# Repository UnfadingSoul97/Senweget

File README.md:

# ⌨️Senweget⌨️
## A split Corne Keyboard that doubles as a stenograph and a fun fidget which your can customise yourself.
Here ig it will look good cute frog keycaps.

Link to Project:https://cad.onshape.com/documents/2615d6a32fd601db65ed9c82/w/49b2a2fd03e5ba3a97975127/e/aca29c1b2985c1fb6079fbe5

---
I was just living my life and i thought hey i can make stuff in cad now and wanted to push my limit and wanted to make something that was not too hard but still new to make.
The tracing process was probably the hardest part i had to experience in this project.

### What does it do??

 It can be used for stenograph,Hotswappable but it HAS **PER-KEY RGB** not that it matters but need to see at Night.
 And can Play Music 🎵
 You can add 🎹,🥁 and you can add custom sounds. One thing am using buzzer cuz i like its buzzing and it cool.
 For ya nerds who know what you are doing.I have left some free GPIOS for connecting stuff ya like.

 ### THE BIRTH 🐵
 I made the Schematic and PCB in KICAD
 **Schematic**

**PCB Design**

**PCB**

## 📋 Frimware
For now i only added for qwerty cuz i really hate writing readme cuz think ADHD idk not tested.
Any way it has standared Qwerty and 1 Knob on each side 
Left one does volume up and down with click as mute
Right one does handles and click also does mute cuz why not.

## How to set up 
Take the bezzle and put on top on the top of the pcb and add your low profile switches then place it on top of the main body according to the tabs then place in the pcb and bexzzle.
and screw it from under the case using 5 M3 screws.the MCU should be facing down on the right side(which means its usb c should face to the downwared direction from the underside of the pcb.
For the left side the top should be facing todwards the pcb and under the PCB ofc
1.Take the PCB and add your switches.
2.Put i it on the body.
 for the right side pcb put the mcu under the pcb which should be facing away form the pcb.
 for the left one the Mcu should be facing towards the pcb otherwise the usb c wont fit.
3.now place in the top bezzle
4.Now u can screw it from the underneath using M3. screw pls check the length of the screw needed cuz idk the exact height after printing.

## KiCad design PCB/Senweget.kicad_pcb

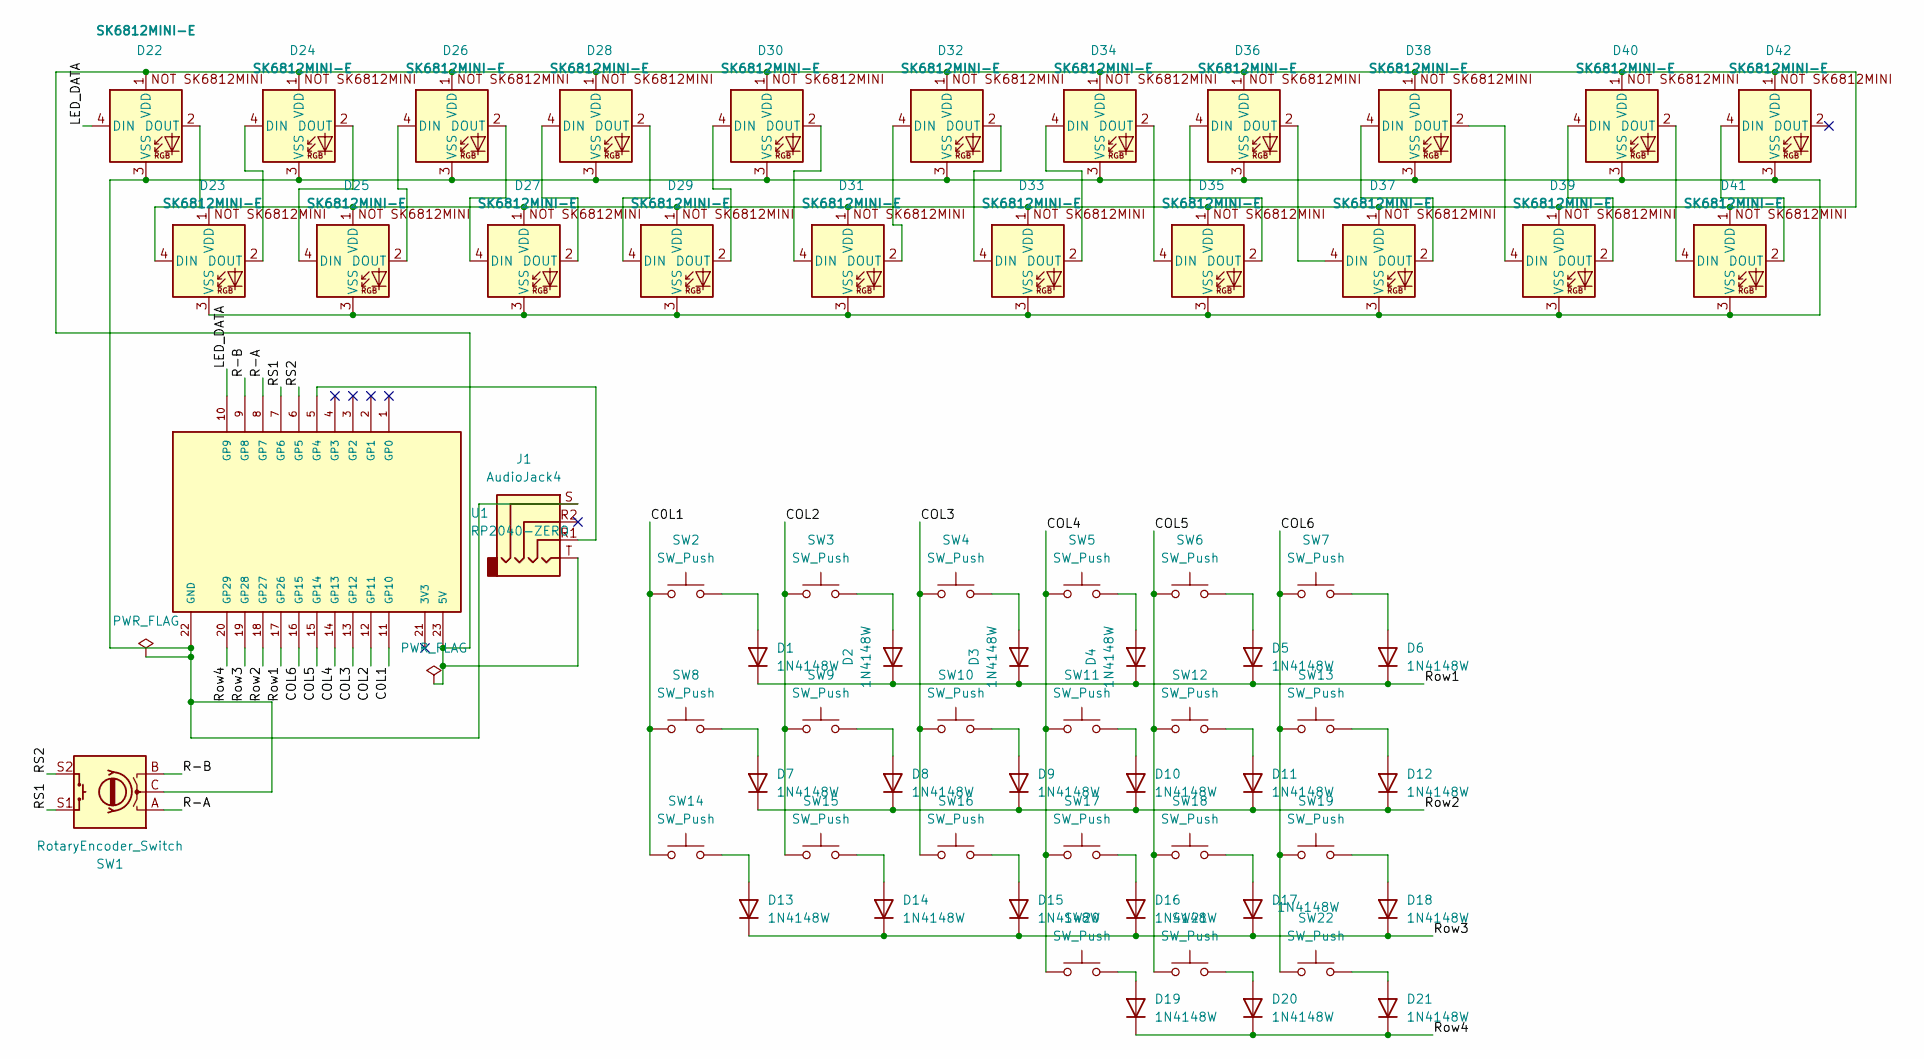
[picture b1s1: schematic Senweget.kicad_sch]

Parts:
D1, D2, D3, D4, D5, D6, D7, D8, D9, D10, D11, D12, D13, D14, D15, D16, D17, D18, D19, D20, D21: 1N4148W; D_SOD-123
D22, D23, D24, D25, D26, D27, D28, D29, D30, D31, D32, D33, D34, D35, D36, D37, D38, D39, D40, D41, D42: SK6812MINI-E; LED_SK6812MINI-E_3.2x2.8mm_P1.5mm_ReverseMount
J1: AudioJack4; Jack_3.5mm_PJ320D_Horizontal
SW1: RotaryEncoder_Switch; RotaryEncoder_Alps_EC11E-Switch_Vertical_H20mm
SW2, SW3, SW4, SW5, SW6, SW7, SW8, SW9, SW10, SW11, SW12, SW13, SW14, SW15, SW16, SW17, SW18, SW19, SW20, SW21, SW22: SW_Push; SW_MX_Kailh_Choc_V1V2_HotSwap_Hybrid_double
U1: RP2040-ZERO; MODULE_RP2040-ZERO; PARTREV NA

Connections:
/C0L1: SW2.1, SW8.1, SW14.1, U1.11 (GP10)
/COL2: SW3.1, SW9.1, SW15.1, U1.12 (GP11)
/COL3: SW4.1, SW10.1, SW16.1, U1.13 (GP12)
/COL4: SW5.1, SW11.1, SW17.1, SW20.1, U1.14 (GP13)
/COL5: SW6.1, SW12.1, SW18.1, SW21.1, U1.15 (GP14)
/COL6: SW7.1, SW13.1, SW19.1, SW22.1, U1.16 (GP15)
/LED_DATA: D22.4 (DIN), U1.10 (GP9)
/R-A: SW1.A, U1.8 (GP7)
/R-B: SW1.B, U1.9 (GP8)
/RS1: SW1.S1, U1.7 (GP6)
/RS2: SW1.S2, U1.6 (GP5)
/Row1: D1.1 (K), D2.1 (K), D3.1 (K), D4.1 (K), D5.1 (K), D6.1 (K), U1.17 (GP26)
/Row2: D7.1 (K), D8.1 (K), D9.1 (K), D10.1 (K), D11.1 (K), D12.1 (K), U1.18 (GP27)
/Row3: D13.1 (K), D14.1 (K), D15.1 (K), D16.1 (K), D17.1 (K), D18.1 (K), U1.19 (GP28)
/Row4: D19.1 (K), D20.1 (K), D21.1 (K), U1.20 (GP29)
unnamed: D1.2 (A), SW2.2
unnamed: D2.2 (A), SW3.2
unnamed: D3.2 (A), SW4.2
unnamed: D4.2 (A), SW5.2
unnamed: D5.2 (A), SW6.2
unnamed: D6.2 (A), SW7.2
unnamed: D7.2 (A), SW8.2
unnamed: D8.2 (A), SW9.2
unnamed: D9.2 (A), SW10.2
unnamed: D10.2 (A), SW11.2
unnamed: D11.2 (A), SW12.2
unnamed: D12.2 (A), SW13.2
unnamed: D13.2 (A), SW14.2
unnamed: D14.2 (A), SW15.2
unnamed: D15.2 (A), SW16.2
unnamed: D16.2 (A), SW17.2
unnamed: D17.2 (A), SW18.2
unnamed: D18.2 (A), SW19.2
unnamed: D19.2 (A), SW20.2
unnamed: D20.2 (A), SW21.2
unnamed: D21.2 (A), SW22.2
unnamed: D22.2 (DOUT), D23.4 (DIN)
unnamed: D22.1 (VDD), D23.1 (VDD), D24.1 (VDD), D25.1 (VDD), D26.1 (VDD), D27.1 (VDD), D28.1 (VDD), D29.1 (VDD), D30.1 (VDD), D31.1 (VDD), D32.1 (VDD), D33.1 (VDD), D34.1 (VDD), D35.1 (VDD), D36.1 (VDD), D37.1 (VDD), D38.1 (VDD), D39.1 (VDD), D40.1 (VDD), D41.1 (VDD), D42.1 (VDD), J1.T, U1.23 (5V)
unnamed: D22.3 (VSS), D23.3 (VSS), D24.3 (VSS), D25.3 (VSS), D26.3 (VSS), D27.3 (VSS), D28.3 (VSS), D29.3 (VSS), D30.3 (VSS), D31.3 (VSS), D32.3 (VSS), D33.3 (VSS), D34.3 (VSS), D35.3 (VSS), D36.3 (VSS), D37.3 (VSS), D38.3 (VSS), D39.3 (VSS), D40.3 (VSS), D41.3 (VSS), D42.3 (VSS), J1.S, SW1.C, U1.22 (GND)
unnamed: D23.2 (DOUT), D24.4 (DIN)
unnamed: D24.2 (DOUT), D25.4 (DIN)
unnamed: D25.2 (DOUT), D26.4 (DIN)
unnamed: D26.2 (DOUT), D27.4 (DIN)
unnamed: D27.2 (DOUT), D28.4 (DIN)
unnamed: D28.2 (DOUT), D29.4 (DIN)
unnamed: D29.2 (DOUT), D30.4 (DIN)
unnamed: D30.2 (DOUT), D31.4 (DIN)
unnamed: D31.2 (DOUT), D32.4 (DIN)
unnamed: D32.2 (DOUT), D33.4 (DIN)
unnamed: D33.2 (DOUT), D34.4 (DIN)
unnamed: D34.2 (DOUT), D35.4 (DIN)
unnamed: D35.2 (DOUT), D36.4 (DIN)
unnamed: D36.2 (DOUT), D37.4 (DIN)
unnamed: D37.2 (DOUT), D38.4 (DIN)
unnamed: D38.2 (DOUT), D39.4 (DIN)
unnamed: D39.2 (DOUT), D40.4 (DIN)
unnamed: D40.2 (DOUT), D41.4 (DIN)
unnamed: D41.2 (DOUT), D42.4 (DIN)
unnamed: J1.R1, U1.5 (GP4)

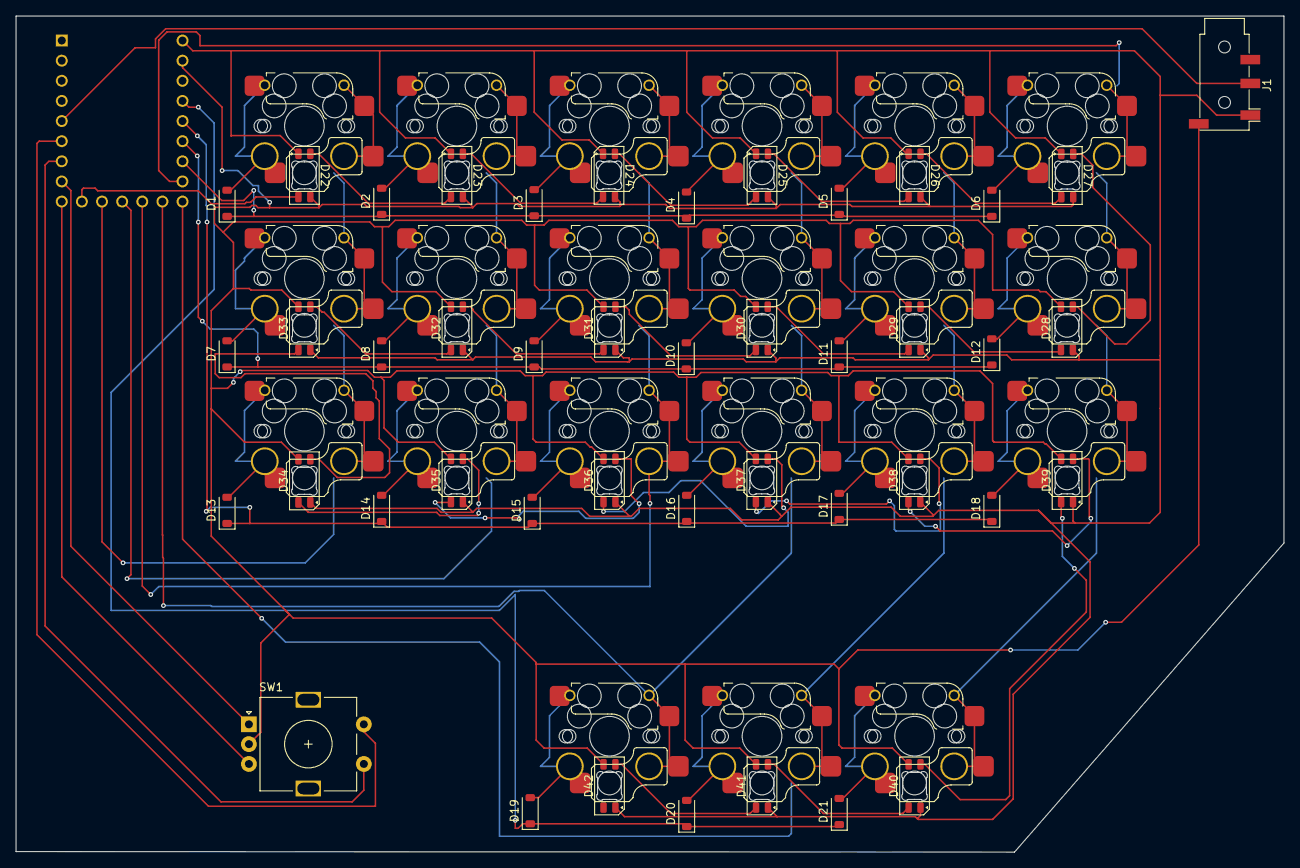
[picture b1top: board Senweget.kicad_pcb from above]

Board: 2 copper layers, 160.0 x 105.5 mm, 66 parts (1 on the bottom side), 59 nets.
